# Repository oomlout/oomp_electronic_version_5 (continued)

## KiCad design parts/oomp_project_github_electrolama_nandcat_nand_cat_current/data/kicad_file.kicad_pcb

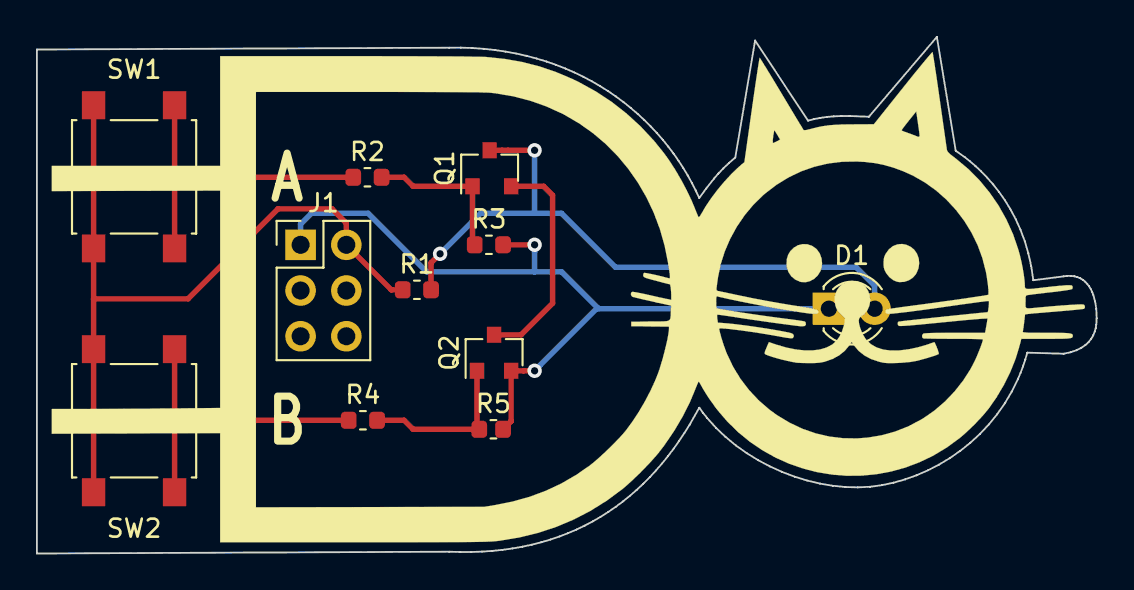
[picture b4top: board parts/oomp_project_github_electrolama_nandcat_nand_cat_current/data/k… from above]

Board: 2 copper layers, 58.9 x 28.7 mm, 11 parts (0 on the bottom side), 8 nets.

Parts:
D1: LED; LED_D3.0mm
J1: Conn_02x03_Odd_Even; PinHeader_2x03_P2.54mm_Vertical
Q1, Q2: BC847B; SOT-23
R1, R2, R4: 1K; R_0603_1608Metric
R3, R5: 100K; R_0603_1608Metric
SW1, SW2: SW_Push; SW_SPST_B3S-1000

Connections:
GND: D1.1, J1.1, Q2.2, R3.2, R5.2
unnamed: D1.2, Q1.3, R1.2
unnamed: Q1.1, R2.2, R3.1
unnamed: Q1.2, Q2.3
unnamed: Q2.1, R4.2, R5.1
unnamed: R2.1, SW1.2
unnamed: R4.1, SW2.2
VCC: J1.2, R1.1, SW1.1, SW2.1
